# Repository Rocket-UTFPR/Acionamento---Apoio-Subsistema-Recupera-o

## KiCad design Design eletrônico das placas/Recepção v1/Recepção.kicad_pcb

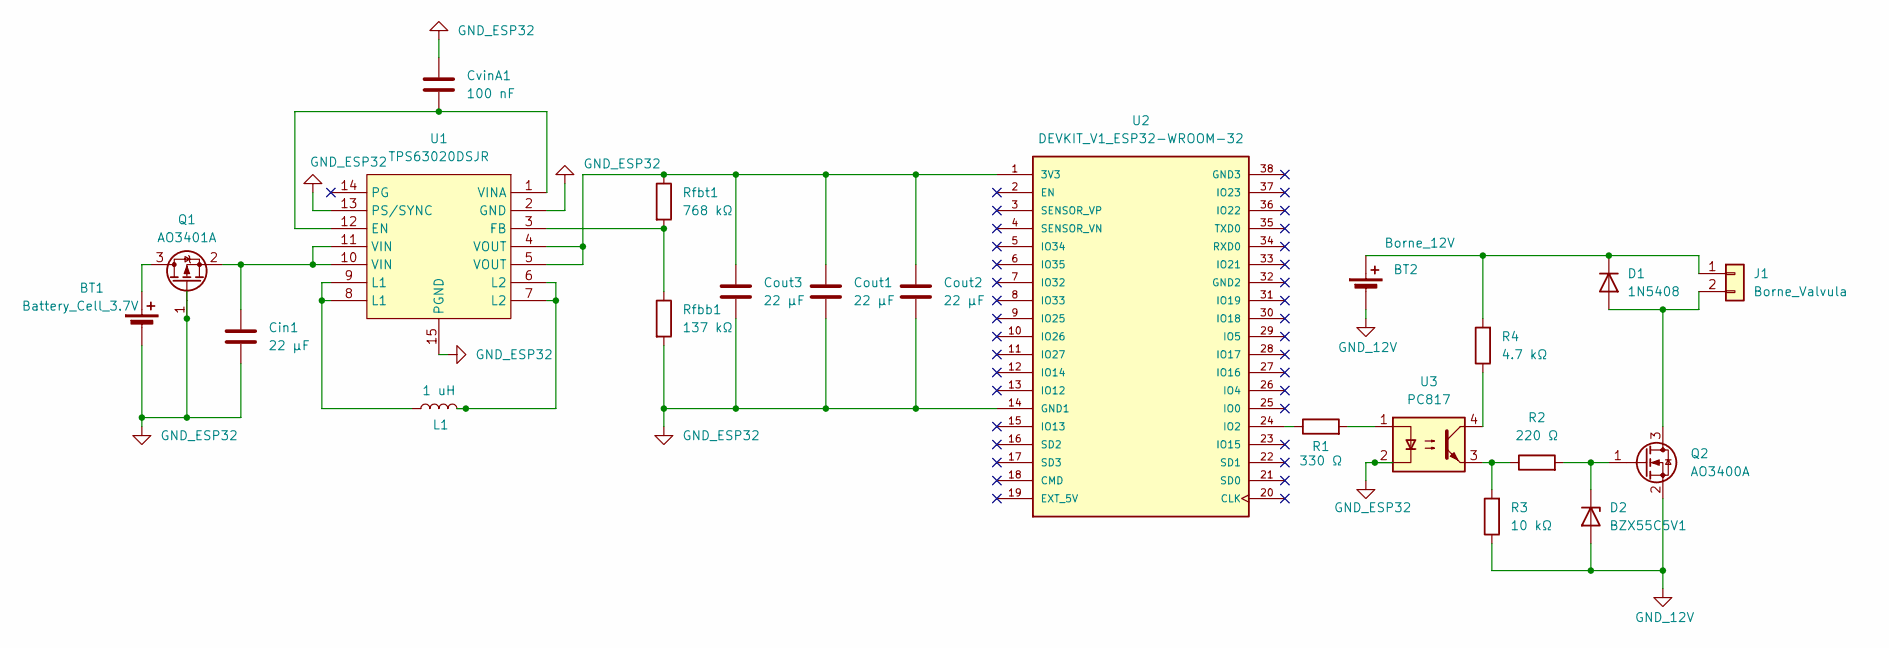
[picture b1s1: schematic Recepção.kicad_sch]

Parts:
BT1: Battery_Cell_3.7V; BatteryHolder_Keystone_1042_1x18650
BT2: Borne_12V; TerminalBlock_Phoenix_PT-1,5-2-5.0-H_1x02_P5.00mm_Horizontal
Cin1: 22 µF; C_0603_1608Metric
Cout1, Cout2, Cout3: 22 µF; C_0603_1608Metric
CvinA1: 100 nF; C_0603_1608Metric
D1: 1N5408; D_DO-201AD_P15.24mm_Horizontal
D2: BZX55C5V1; D_DO-35_SOD27_P7.62mm_Horizontal
J1: Borne_Valvula; TerminalBlock_Phoenix_PT-1,5-2-5.0-H_1x02_P5.00mm_Horizontal
L1: 1 uH; IND_DFE252012F-1R0M=P2_MUR
Q1: AO3401A; SOT-23
Q2: AO3400A; SOT-23
R1: 330 Ω; R_Axial_DIN0207_L6.3mm_D2.5mm_P7.62mm_Horizontal
R2: 220 Ω; R_Axial_DIN0207_L6.3mm_D2.5mm_P7.62mm_Horizontal
R3: 10 kΩ; R_Axial_DIN0207_L6.3mm_D2.5mm_P7.62mm_Horizontal
R4: 4.7 kΩ; R_Axial_DIN0207_L6.3mm_D2.5mm_P7.62mm_Horizontal
Rfbb1: 137 kΩ; R_0402_1005Metric
Rfbt1: 768 kΩ; R_0805_2012Metric
U1: TPS63020DSJR; VSON-14_L4.0-W3.0-P0.50-BL-EP_TI_DSJ; MPN TPS63020DSJR; LCSC Part C15483
U2: DEVKIT_V1_ESP32-WROOM-32; MODULE_DEVKIT_V1_ESP32-WROOM-32; PARTREV N/A
U3: PC817; DIP-4_W7.62mm

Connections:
GND_12V: BT2.2 (-), D2.2 (A), Q2.2 (S), R3.1
GND_ESP32: BT1.2 (-), Cin1.2, Cout1.2, Cout2.2, Cout3.2, CvinA1.2, Q1.1 (G), Rfbb1.2, U1.2 (GND), U1.13 (PS/SYNC), U1.15 (PGND), U2.14 (GND1), U3.2
unnamed: BT1.1 (+), Q1.3 (D)
unnamed: BT2.1 (+), D1.1 (K), J1.1, R4.2
unnamed: D1.2 (A), J1.2, Q2.3 (D)
unnamed: D2.1 (K), Q2.1 (G), R2.2
unnamed: L1.1, U1.8 (L1), U1.9 (L1)
unnamed: L1.2, U1.6 (L2), U1.7 (L2)
unnamed: Cin1.1, Q1.2 (S), U1.10 (VIN), U1.11 (VIN)
unnamed: R1.2, U3.1
unnamed: R2.1, R3.2, U3.3
unnamed: R4.1, U3.4
unnamed: CvinA1.1, U1.1 (VINA), U1.12 (EN)
unnamed: Rfbb1.1, Rfbt1.2, U1.3 (FB)
unnamed: Cout1.1, Cout2.1, Cout3.1, Rfbt1.1, U1.4 (VOUT), U1.5 (VOUT), U2.1 (3V3)
unnamed: R1.1, U2.24 (IO2)

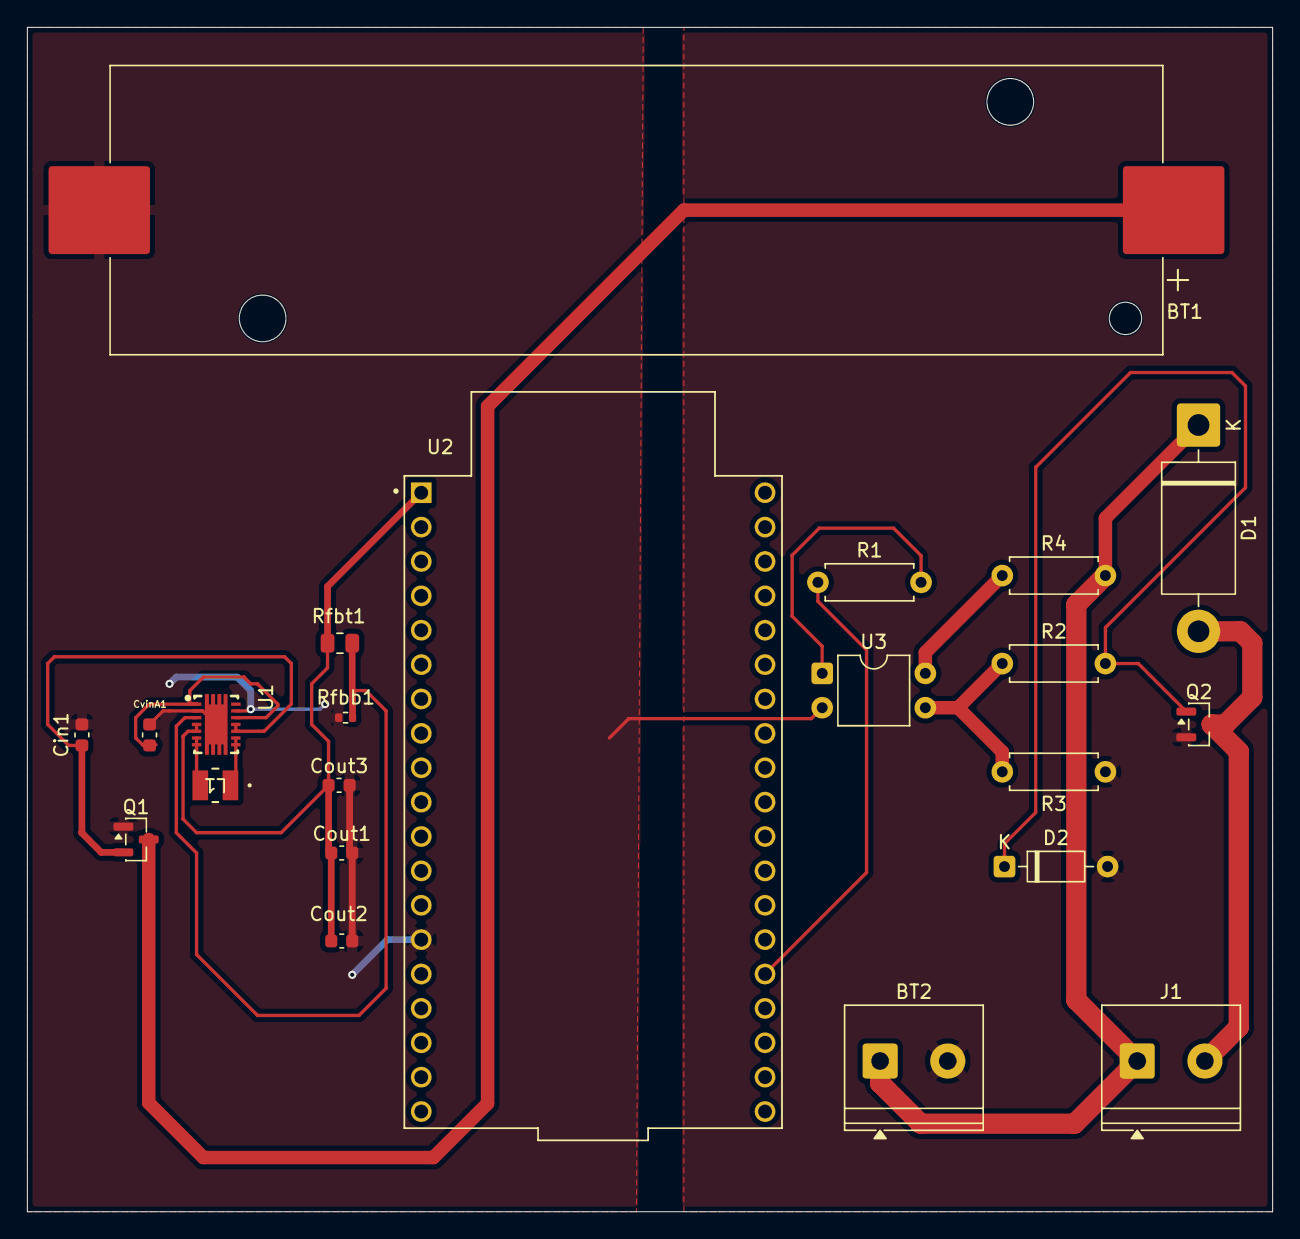
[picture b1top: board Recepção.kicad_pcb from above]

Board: 2 copper layers, 92.0 x 87.5 mm, 22 parts (0 on the bottom side), 16 nets.
